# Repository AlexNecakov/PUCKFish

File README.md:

## Welcome to PUCKFish!
Design Team: Will Aracri, Peter Ha, Ammar Hussain, Alex Necakov, Victoria Thomas
### Please view our [wiki](https://github.com/AlexNecakov/PUCKFish/wiki) for more information, including the hardware and software READMEs!

## Introduction
PUCKFish is an underwater array of sensors meant to characterize underwater environments by sensing important information, designed for the 2021-2022 senior design project at Boston University. Originally designed to track lobsters, this device measures pressure, temperature, dissolved oxygen levels, ambient light, salinity and current speed as well as direction. The system is fully waterproof and meant to survive pressures found at a depth of around 1000 feet and survive for 10 days without a recharge. Data collection begins automatically after submersion and transmits the data collected to a base station via radio. PUCKFish can be built on a budget of around $150. This document will walk you through the PUCKFish design project, tips, and lessons learned. This document will also point you to other areas on the Github for more information about the relevant subsystems.

## Design Process
The architecture of PUCKFish optimized for two priorities, cost and survivability. From these priorities, three major challenges were identified.

1. PCB and Electronics Design: Any electronics used must have low-current draw. Electronics must also be recharged without introducing a risk of water-intrusion. Any sensors used must be low-cost.
2. Sensing Current Speed and Direction: Any method used to measure current speed and direction must be robust and simple.
3. Enclosure Design: Enclosure must be able to protect against high-pressure environments as well as protect electronics from saltwater intrusion.
Any design change should carefully consider these challenges and decide on the appropriate trade offs to achieve survivability and a low cost.

## PCB and Electronics Design
PUCKFish must read 6 different metrics from onboard sensors, store the data locally, transmit the data to a shipboard, and be rechargeable. Our software is written in C using the Arduino Framework and can be easily installed, modified, built and uploaded following instructions found on the [Software Overview](https://github.com/AlexNecakov/PUCKFish/wiki/Software-Overview) page of our wiki. Our main software can be found in the [/FlagpoleClient](https://github.com/AlexNecakov/PUCKFish/tree/master/FlagpoleClient) directory. Our electronics hardware consists of several sensors, a LiPo battery, SD card, and Adafruit Feather M0 with LoRa radio to control the system/broadcast data over the LoRa 900 mHz frequency. All of these components were put together on a custom PCB designed in Eagle. The PCB currently lacks a location for the SD card and Dissolved Oxygen sensor to be includeded, and should be added in future versions of this project. Information about our hardware, including sensor vendor links and specifications, data sheets, and renders of our PCB layouts can be found on the [Hardware Overview](https://github.com/AlexNecakov/PUCKFish/wiki/Hardware-Overview) wiki page. PCB project information can be found in the [/PCB/Eagle Project](https://github.com/AlexNecakov/PUCKFish/tree/master/PCB/Eagle%20Project) directory.

PUCKFish uses Qi wireless charging in order to replenish the battery. Using wireless charging eliminates the possibility of water-intrusion or corroded charging leads. 

PUCKFish uses several sensors to collect data. Information on the sensors may be found in the [Hardware Overview](https://github.com/AlexNecakov/PUCKFish/wiki/Hardware-Overview) page and the software mounted on them may be found in the [Software Overview](https://github.com/AlexNecakov/PUCKFish/wiki/Software-Overview) page. These sensors were selected due to price, power draw, supply voltage, measurement range, and waterproof capabilities.

PUCKFish uses a LoRa capable radio to transmit data over the 900 mHz frequency in JSON formatted packets. This radio is mounted to the Feather Board and begins sending the data once the PUCKFish has surfaced from the ocean. For more information on the radio, see the [Hardware Overview](https://github.com/AlexNecakov/PUCKFish/wiki/Hardware-Overview) page for the specifications of the hardware and the [Software Overview](https://github.com/AlexNecakov/PUCKFish/wiki/Software-Overview) page for the software that is used to collect/transmit the data.

Several sensors require access to the water to measure their respective characteristics. The pressure sensor uses a -08 O-ring to attach a vinyl tube which then leads to the exterior while pouring the epoxy. The salinity sensor uses two wire leads that sense the current produced between them, which then calculates the salinity. These wire leads must be exposed when pouring the epoxy. The dissolved oxygen sensor contains a galvanic probe. This probe must be prepped with a chemical provided from the sensor manufacturer. This probe must also be exposed while pouring the epoxy. As discussed below, silicone mold has a hole that these sensors can be routed through to ensure they will have access to water after the epoxy is poured.

## Sensing Current Speed and Direction
PUCKFish uses an IMU to measure current speed and direction. As PUCKFish is sphere, its position in the water heavily impacts the orientation and current data that is collects. Other methods of measuring current, like weather vanes or flow tubes, are too delicate and are unable to operate for long periods underwater with any degree of reliability. The design of PUCKFish’s enclosure can be found below. Information about the IMU implementation can be found in the wiki in both the [Hardware Overview](https://github.com/AlexNecakov/PUCKFish/wiki/Hardware-Overview) and [Software Overview](https://github.com/AlexNecakov/PUCKFish/wiki/Software-Overview) pages.

## Enclosure Design
PUCKFish uses a 3D Printed skeleton to hold electronic components and is encased within an epoxy shell. Sensors that need access to the water protrude from the epoxy shell in order to successfully measure the required components.

The 3D printed skeleton is the product of several steps of iteration to fit the PCB and accommodate the Qi wireless charging receiver. Once the skeleton is printed on an FDM printer with ABS filament, it requires no extra manufacturing steps. Inserting the PCB is simple as the skeleton was sized specifically to accommodate this element. For more information on the 3D printed skeleton, view relevant documentation in the [Hardware Overview](https://github.com/AlexNecakov/PUCKFish/wiki/Hardware-Overview) page.

The epoxy shell was developed specifically with survivability and cost in mind. Metallic or plastic structures containing the electronics introduce the problem of seams connecting the devices. In each of these cases, expensive manufacturing techniques, as well as complex sealing procedures, are damaging to both cost and survivability. Manufacturing the epoxy shell requires a series of two molds to form, one mold that forms the final silicone form, and the final silicone form that creates the epoxy shell. It is essential that the silicone mold is used to form the epoxy casing, as 3D printed molds are too porous for the epoxy to form in and other machined elements are too costly to make. To find the mold’s as well as the mold making process, go to the [Hardware Overview](https://github.com/AlexNecakov/PUCKFish/wiki/Hardware-Overview) page or find the relevant CAD models [/Structure Cad](https://github.com/AlexNecakov/PUCKFish/tree/master/Structure%20CAD) directory.

## Manufacturing PUCKFish
For a general description of how to manufacture PUCKFish follow the instructions below.
1. First, populate the PCB with the required components as shown in the [Hardware Overview](https://github.com/AlexNecakov/PUCKFish/wiki/Hardware-Overview)
2. Build and upload the FlagpoleClient program to the Feather Board as described in the [Software Overview](https://github.com/AlexNecakov/PUCKFish/wiki/Software-Overview)
3. 3D print the PCB skeleton for the electronics.
4. 3D print the silicone mold molds.
5. Pour the silicone molds for epoxy. 
6. Install the populated PCB into the 3D printed skeleton
7. Install the aluminum block into the top of the 3D printed skeleton with epoxy
8. Screw in the eyebolt to the aluminum block.
9. Install the 3D printed skeleton with populated PCB into the silicone mold, with the eyebolt pointed through the mold.
10. Pour epoxy into the silicone mold in three parts. DO NOT POUR EPOXY IN ONE BATCH (The heat for the epoxy may damage electrical components)
11. Wait three days in between epoxy cures. The device is ready to operate after charging after the last cure period.

## Operation
See our [wiki](https://github.com/AlexNecakov/PUCKFish/wiki) or [Users Manual](https://github.com/AlexNecakov/PUCKFish/blob/master/Reports/Users%20Manual.docx) for additional information on how to operate PUCKFish.

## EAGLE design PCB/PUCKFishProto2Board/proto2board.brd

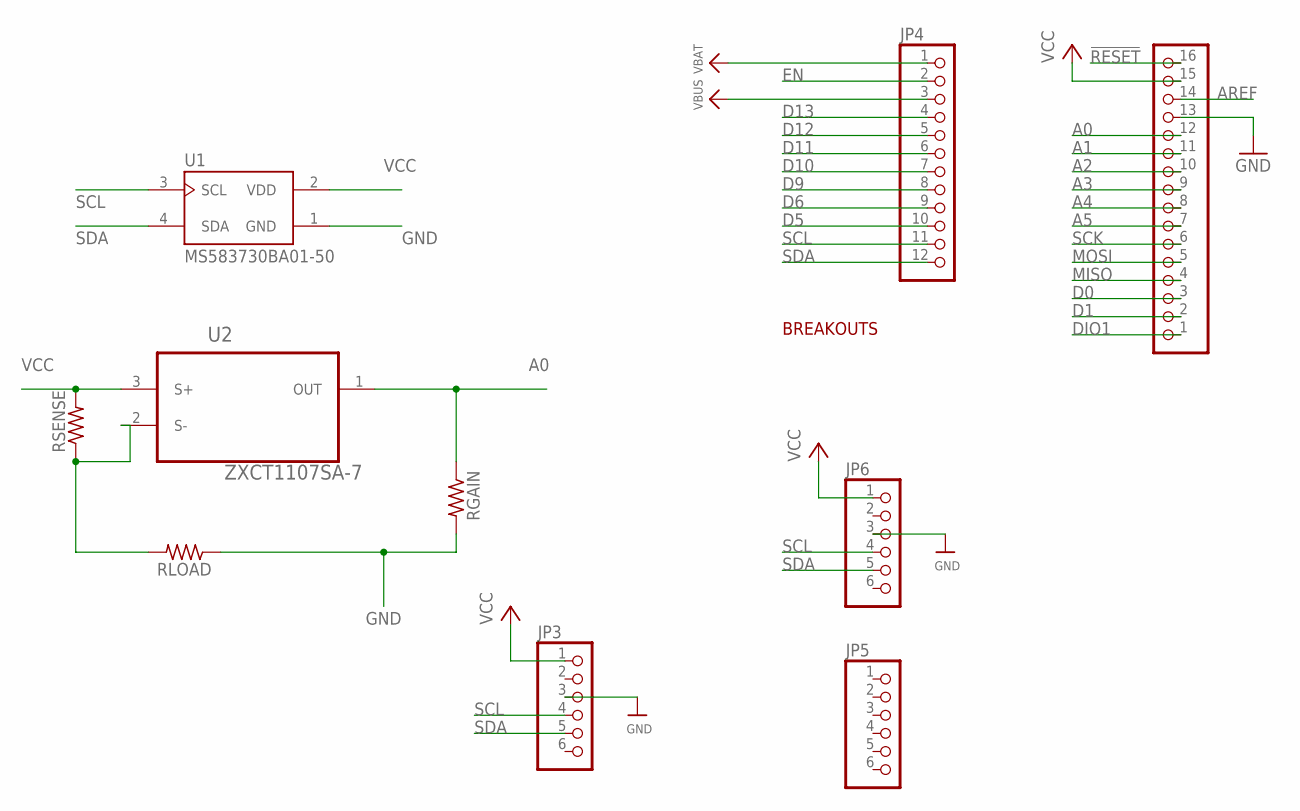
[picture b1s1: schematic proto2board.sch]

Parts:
JP2: HEADER-1X16ROUND; 1X16_ROUND
JP3, JP6: HEADER-1X670MIL; 1X06_ROUND_70
JP4: HEADER-1X12; 1X12_ROUND
JP5: HEADER-1X6ROUND; 1X06_ROUND
RGAIN: R-US_0204/7; 0204/7
RLOAD: R-US_0204/7; 0204/7
RSENSE: R-US_0204/7; 0204/7
U1: MS583730BA01-50; TE_MS583730BA01-50
U2: ZXCT1107SA-7; SOT91P240X110-3N

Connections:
!RESET: JP2.16
A0: JP2.12, RGAIN.1, U2.1 (OUT)
A1: JP2.11
A2: JP2.10
A3: JP2.9
A4: JP2.8
A5: JP2.7
AREF: JP2.14
D0: JP2.3
D1: JP2.2
D5: JP4.10
D6: JP4.9
D9: JP4.8
D10: JP4.7
D11: JP4.6
D12: JP4.5
D13: JP4.4
DIO1: JP2.1
EN: JP4.2
GND: JP2.13, JP3.3, JP6.3, RGAIN.2, RLOAD.1, U1.1 (GND)
MISO: JP2.4
MOSI: JP2.5
unnamed: RLOAD.2, RSENSE.1, U2.2 (S-)
SCK: JP2.6
SCL: JP3.4, JP4.11, JP6.4, U1.3 (SCL)
SDA: JP3.5, JP4.12, JP6.5, U1.4 (SDA)
VBAT: JP4.1
VBUS: JP4.3
VCC: JP2.15, JP3.1, JP6.1, RSENSE.2, U1.2 (VDD), U2.3 (S+)

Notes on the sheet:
BREAKOUTS

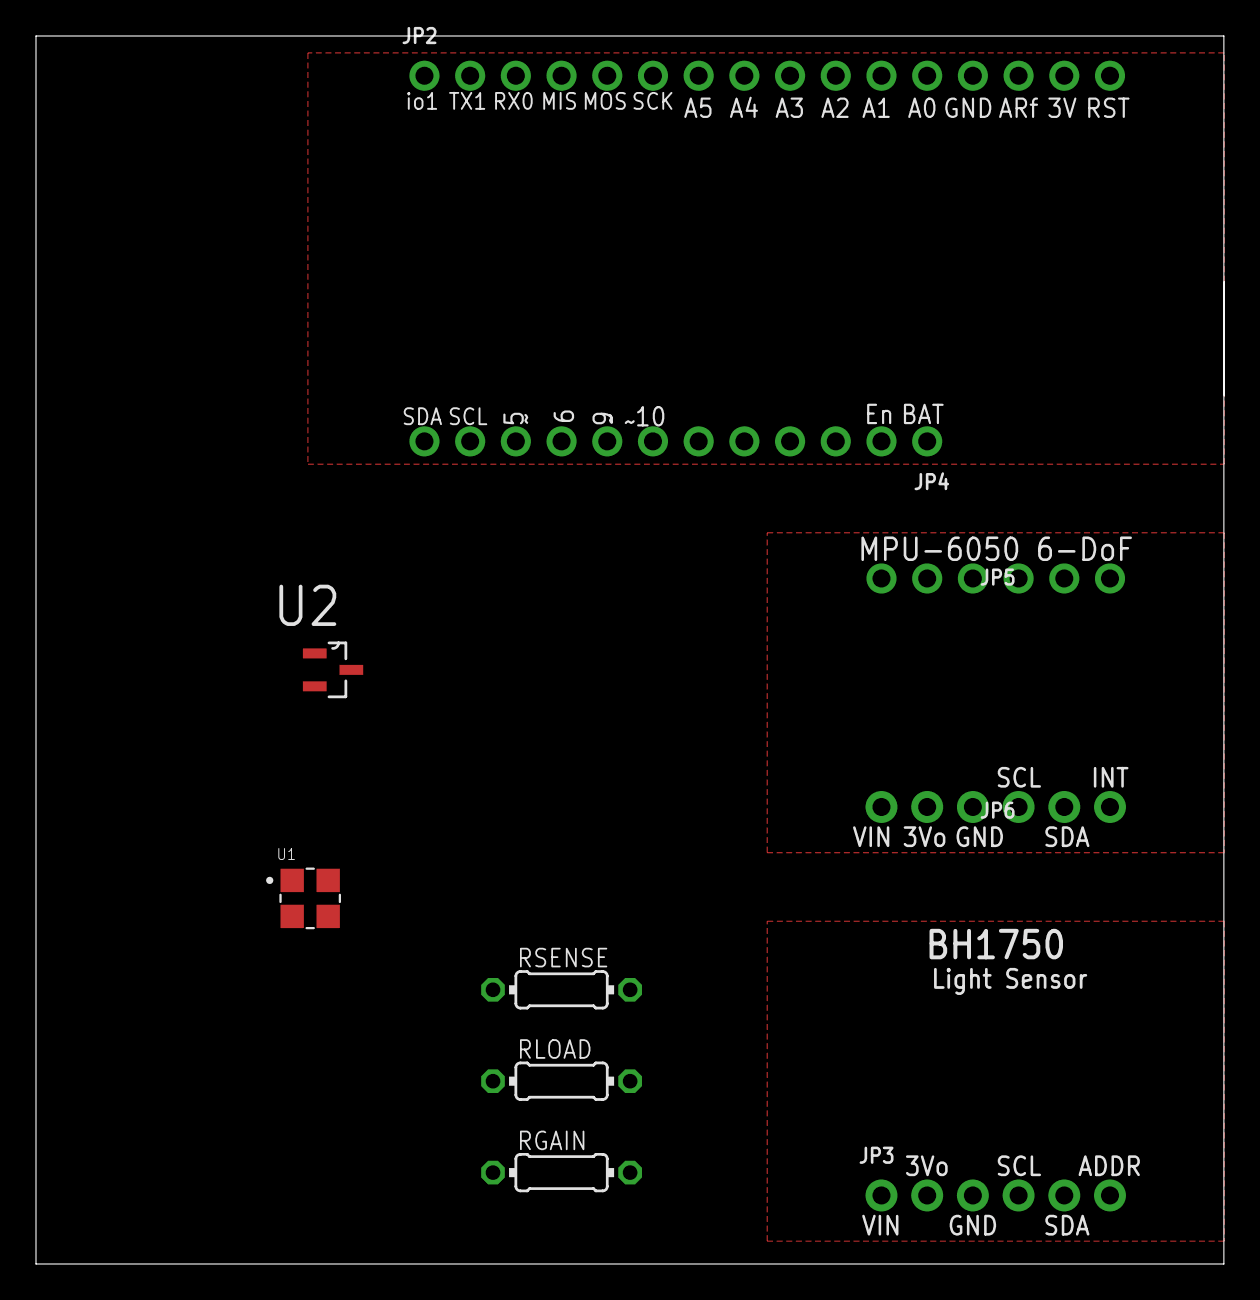
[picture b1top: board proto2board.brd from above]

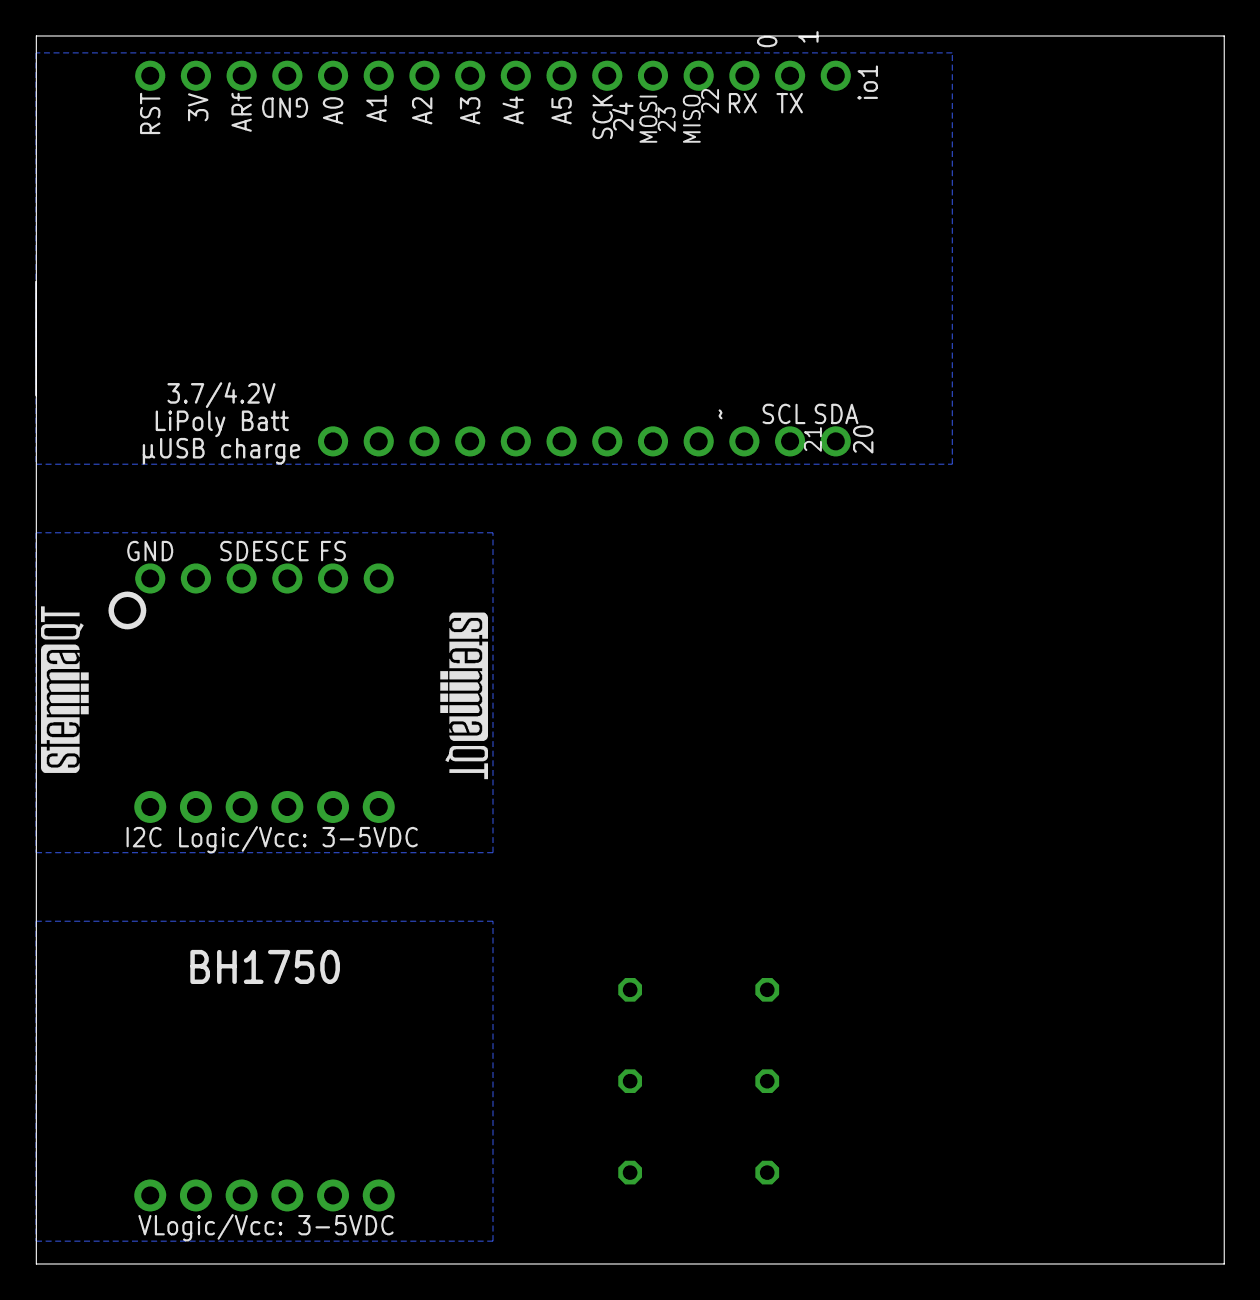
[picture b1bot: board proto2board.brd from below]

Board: 2 copper layers, 66.0 x 68.2 mm, 13 parts (3 on the bottom side), 6 nets.

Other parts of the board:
U$6: PCBFEAT-REV-040
U$7, U$8: STEMMAQT

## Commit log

2021-09-27 initial commit
    adding pdrr docs
2021-09-28 Added first logbook entry for Alex
2021-09-29 log entry 2
2021-10-02 Meeting 9/27
    These are my meeting notes from our meeting on 9_27
2021-10-02 Added logbook entry
2021-10-04 Will's Commit
    Introducing a folder for my notes as well as our competitive analysis
2021-10-04 logbook 4
2021-10-04 Switched this file over to plaintext
2021-10-05 logbook
2021-10-06 Final PDRR pres added
2021-10-18 Uploading LaTeX source with bibliography
2021-10-19 Added ECE Systems Diagram
2021-10-19 Final edits to report
2021-10-20 Adding Shark Tank pres to repo,
    Don't need this on drive anymore
2021-10-22 Making PlatformIO project for Flagpole IMU test
2021-10-26 drivers for testbed IMU
2021-11-06 create base station, added radiohead library
2021-11-06 using platformio's built in lib finder
2021-11-07 client imu driver working
2021-11-09 very important commit
2021-11-16 battery life monitor
2021-11-29 Team work breakdown/contract
2021-11-30 Added orientation to client and uploaded test data
2021-11-30 Added my paragraph to contract and signed it
2021-12-01 Add files via upload
    Added my paragraph
2021-12-01 Filled and signed team agreement
2021-12-01 Uploaded Pill images
2021-12-03 Uploaded PDR slides
2021-12-11 Create Will's Notes
2021-12-12 not tracking this anymore
    don't repeat yourself
2022-01-23 CAD of Skeleton
    This is the CAD of the skeleton that will be 3D printed and will fit into the epoxied sphere.
2022-01-23 Add files via upload
    Eagle PCB design files for each component
2022-01-24 Added all parts to new Eagle Project/created DBLs for Adafruit stuff
2022-01-24 Schematic done except salinity sensor
2022-01-24 Reduced board size
2022-01-25 Salinity incorporated into sch better now
    Resistors added, needs proofreading
2022-01-25 Updates to the Skeleton Design
2022-01-25 Skeleton Updates
2022-01-25 Mold CAD first draft
2022-01-25 cleaned up model
2022-01-25 lil baby mold
2022-01-26 assembly
2022-01-27 Add files via upload
    Preliminary layout
2022-01-28 Skeleton Update
2022-01-28 updated assembly, mold to skeleton 7
2022-01-31 Final Skeleton Update
2022-02-01 Skeleton 8 with small details
2022-02-03 added versions for printing
2022-02-07 mpu and bh sensors from example code
2022-02-08 Fixed DRC errors
2022-02-10 Fixed angles
2022-02-10 Latest updates
2022-02-13 PCB Layout editing
    Vialess layout, exported in the zip file and being sent to JLC now
2022-02-27 metamolds!
2022-02-27 uploaded stls
2022-02-27 Redoing client code for prototype 2
2022-02-28 prototype salinity sensor driver
2022-02-28 zxct prototype put into main
2022-02-28 json formatting prototype code
2022-02-28 json formatting and receive handling
2022-03-01 Change in Skeleton8
    Change in skeleton 8 design
2022-03-01 Folder Rename and Test 2 upload
2022-03-01 Add files via upload
    Updated to include salinity equations
2022-03-01 very bad changeset for prototype 2 working demo
2022-03-01 less terrible proto 2 demo code
2022-03-15 Finalized cad(?)
2022-03-18 Updated salinity
2022-03-22 ms5 driver initial commit
2022-03-22 pressure sensor i2c driver
2022-03-22 pressure code in main
2022-03-23 storage first pass
2022-03-24 compiles now. zxct driver needs to be totally rewritten
2022-03-24 ehfhfhsslasdfjjlasdf
2022-03-24 fsm logic
2022-03-24 storage/transmit code
2022-03-24 writing to sd working
2022-03-25 remove delay in ms5
2022-03-25 ms5 reset not working
2022-03-25 ms5 not showing up in i2c scanner.... that is bad
2022-03-25 ms5 driver fixed
2022-03-25 talking to all sensors. sd not working
2022-03-25 ms5 is reading out garbage calib and adc nums
2022-03-25 trying sdfat library
2022-03-26 sd works now, needed to disable radio spi
2022-03-27 fixed no returns in do driver functions
2022-03-27 dumping helper. verified writing to storage
2022-03-27 no longer hard coding file name
2022-03-28 zxct driver equations
2022-03-28 forgot multisampling
2022-03-28 sending bulk packets working
2022-03-28 ms5 driver still doesnt work
2022-03-31 sd driver clears storage on start
2022-03-31 "final testing code" before epoxy pour
2022-04-08 skellyton nin3
2022-04-08 updated moldz
2022-04-11 testing unit 2
2022-04-12 continued unit 2 testing
2022-04-20 fixed some mini bugs
2022-04-21 trying alt driver
2022-04-21 using alt ms5 driver
2022-04-21 fixed packet clipping
2022-04-22 adding back state switch
2022-04-25 state machine code uncommented and pressure tolerance changed
2022-04-26 xzdbfvdfzgbzdf
2022-04-26 poster resources
2022-04-28 final (he says optimistically) client code
2022-04-29 readme sw
2022-04-29 Monte carlo sim of trap distribution
2022-04-29 Repo cleaning for submission
    Added missing reports, cleaned up structure, etc.
2022-04-29 pretty heatmap
2022-04-29 moving to wiki
2022-04-29 removed pcb build files from git
2022-04-29 temp main readme change
2022-04-30 putting this delay in here, its not in unit 2
2022-04-30 renaming these for md
2022-04-30 Charging Dock for PUCKFish, Potential 3D print
2022-05-05 serial monitor over node working
2022-05-05 parsing all but timestamp
2022-05-05 got timestamp
2022-05-06 sending to web client. currently freezing
2022-05-06 graphs working, need css work
2022-05-06 all graphs exist, layout needs work
2022-05-06 added var for serialpath
2022-05-06 layout better
2022-05-06 stylesheet done
2022-05-06 colors and tooltips better locking in for ece day
2022-05-06 Credit statements added
2022-05-06 changed height for ece day
2022-05-09 update gitignore
2022-05-09 untracking node modules
2024-11-16 removed dupes and builds
2024-11-16 fixed vulnerability package
2024-11-16 removed some more text libs

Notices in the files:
parts and their libraries:
microbuilder: This work is placed in the public domain, and may be freely used for commercial and non-commercial work with the following conditions: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
